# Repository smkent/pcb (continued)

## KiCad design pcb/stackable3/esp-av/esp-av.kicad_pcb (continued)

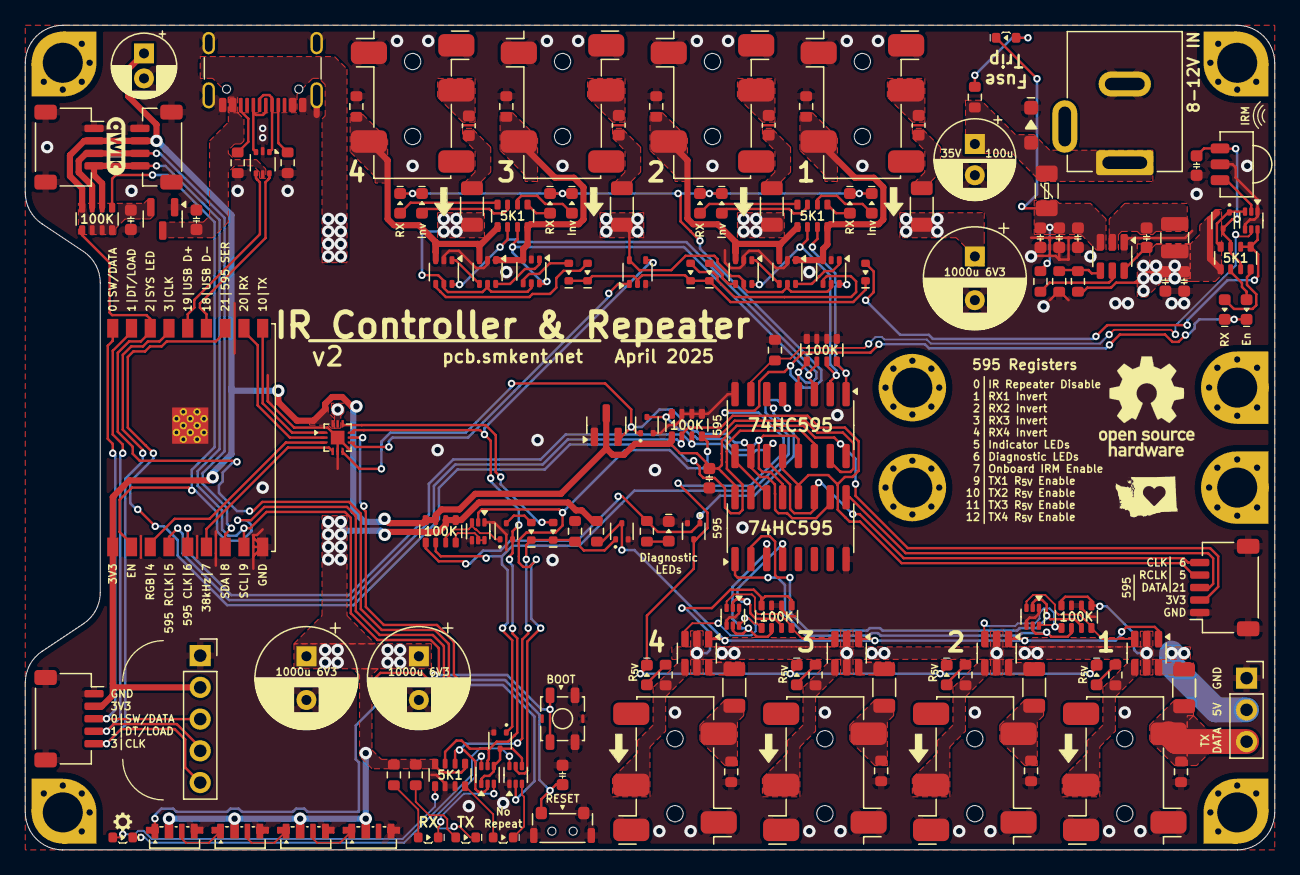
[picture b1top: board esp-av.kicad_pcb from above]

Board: 2 copper layers, 100.0 x 66.0 mm, 146 parts (0 on the bottom side), 124 nets.

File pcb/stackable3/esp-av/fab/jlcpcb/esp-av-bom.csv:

Comment,Designator,Footprint,LCSC
0u1,"C12,C13",discrete:C_0603_1608Metric,
JST SH,J10,connector:JST_SH_SM05B-SRSS-TB_1x05-1MP_P1.00mm_Horizontal,C7433426
USBLC6-2P6,U1,Package_TO_SOT_SMD:SOT-666,C29780639
1u,"C1,C2,C4,C5",discrete:C_0603_1608Metric,
16V 2A,F1,discrete:Fuse_1206_3216Metric,C2982271
ESP32-C3-WROOM-02,SM1,module:ESP32-C3-WROOM-02,
10u,"C3,C10,C11",discrete:C_0603_1608Metric,
Qwiic,J12,connector:Qwiic-SMD-horizontal-logo,C19270571
1000u,"C6,C7,C8",Capacitor_SMD:CP_Elec_8x10,C311227
57K6,R8,Resistor_SMD:R_0603_1608Metric,C23082
74HC595,"U12,U13",Package_SO:SOIC-16_3.9x9.9mm_P1.27mm,
Boot,SW2,Button_Switch_SMD:SW_SPST_TL3342,
Reset,SW1,electromechanical:SW_Push_1P1T-MP_NO_4.6x3mm_Horizontal,C2888932
USB_C_Receptacle_USB2.0_16P,J1,connector:USB_C_Receptacle_GCT_USB4105-xx-A_16P_TopMnt_Horizontal,C2765186
22u,"C14,C15,C19,C20,C21,C22",discrete:C_0603_1608Metric,
5K1,"R1,R2,R16,R18,R19,R20,R22",Resistor_SMD:R_0603_1608Metric,
ME6211C33M5,U2,Package_TO_SOT_SMD:SOT-23-5,C82942
TPS563201,U3,Package_TO_SOT_SMD:SOT-23-6,C116592
10K,"R3,R9",Resistor_SMD:R_0603_1608Metric,
D_TVS,D0,package:D_SOD-123F,C7473216
Pin Socket,J15,Connector_PinSocket_2.54mm:PinSocket_1x03_P2.54mm_Vertical,
Pin socket,J14,Connector_PinSocket_2.54mm:PinSocket_1x05_P2.54mm_Vertical,
4u7,L1,discrete:L_1008_2520Metric,C22471106
XL-1606SURC,LED0,discrete:LED_SideEmitter_1.7x1.1mm,C965860
Qwiic,J13,connector:Qwiic-SMD-vertical,C22390103
DC-005,J0,connector:BarrelJack_DC-005_THT_Horizontal,
Pin socket,J16,Connector_PinSocket_2.54mm:PinSocket_1x07_P2.54mm_Vertical,
1K,R4,Resistor_SMD:R_0603_1608Metric,
100K,"RN3,RN4",discrete:R_Array_Convex_4x0603_HandSolder,C110374
STEMMA-Signal,J11,connector:STEMMA-Signal-SMD-horizontal,C5372880
470u,C16,Capacitor_SMD:CP_Elec_8x10,C7471889
5K1,"RN1,RN5,RN6",discrete:R_Array_Convex_4x0603_HandSolder,C711414
10K,RN2,discrete:R_Array_Convex_4x0603_HandSolder,C110924
PDNM6ET20V05,"Q1,Q7,Q8,Q9",Package_TO_SOT_SMD:SOT-563,C918811
SK6812SIDE-A,"PIX1,PIX2,PIX3,PIX4",discrete:LED_SK6812SIDE-A_4.0x1.6mm,C2890037
SN74LVC1T45Z6,"U10,U11",Package_TO_SOT_SMD:SOT-563,C441819
XL-1606UBC,"LED3,LED4",discrete:LED_SideEmitter_1.7x1.1mm,C965865
XL-1606UWC,"LED1,LED2",discrete:LED_SideEmitter_1.7x1.1mm,C965866
100K,"R5,R6,R7,R17,R21,R23",Resistor_SMD:R_0603_1608Metric,
DMG6968U,Q2,Package_TO_SOT_SMD:SOT-23,C150759
Warm White,LED13,discrete:LED_0603_1608Metric,C2827262
Pink,"LED9,LED10,LED11,LED12,LED14,LED15,LED16,LED17",discrete:LED_0603_1608Metric,C7496826
SN74LVC1G157DC,"U6,U7,U8,U9",package:SOT-363_SC-70-6_HandSolder,C22469913
1N4148WS,"D1,D2,D3,D4,D5,D6",package:D_SOD-323,
PJ-327U,"J2,J3,J4,J5,J6,J7,J8,J9",connector:Jack_3.5mm_PJ-327U-SMT_Horizontal,C397453
Ice Blue,"LED5,LED6,LED7,LED8",discrete:LED_0603_1608Metric,
NC7WZ14P6X,"U4,U5",package:SOT-363_SC-70-6_HandSolder,C5207816
15R4,"R12,R13,R14,R15",Resistor_SMD:R_1206_3216Metric,C3013373
DMP1045U,"Q3,Q4,Q5,Q6,Q10,Q11,Q12,Q13,Q14",Package_TO_SOT_SMD:SOT-23,C177033
2K2,"R10,R11",Resistor_SMD:R_0603_1608Metric,

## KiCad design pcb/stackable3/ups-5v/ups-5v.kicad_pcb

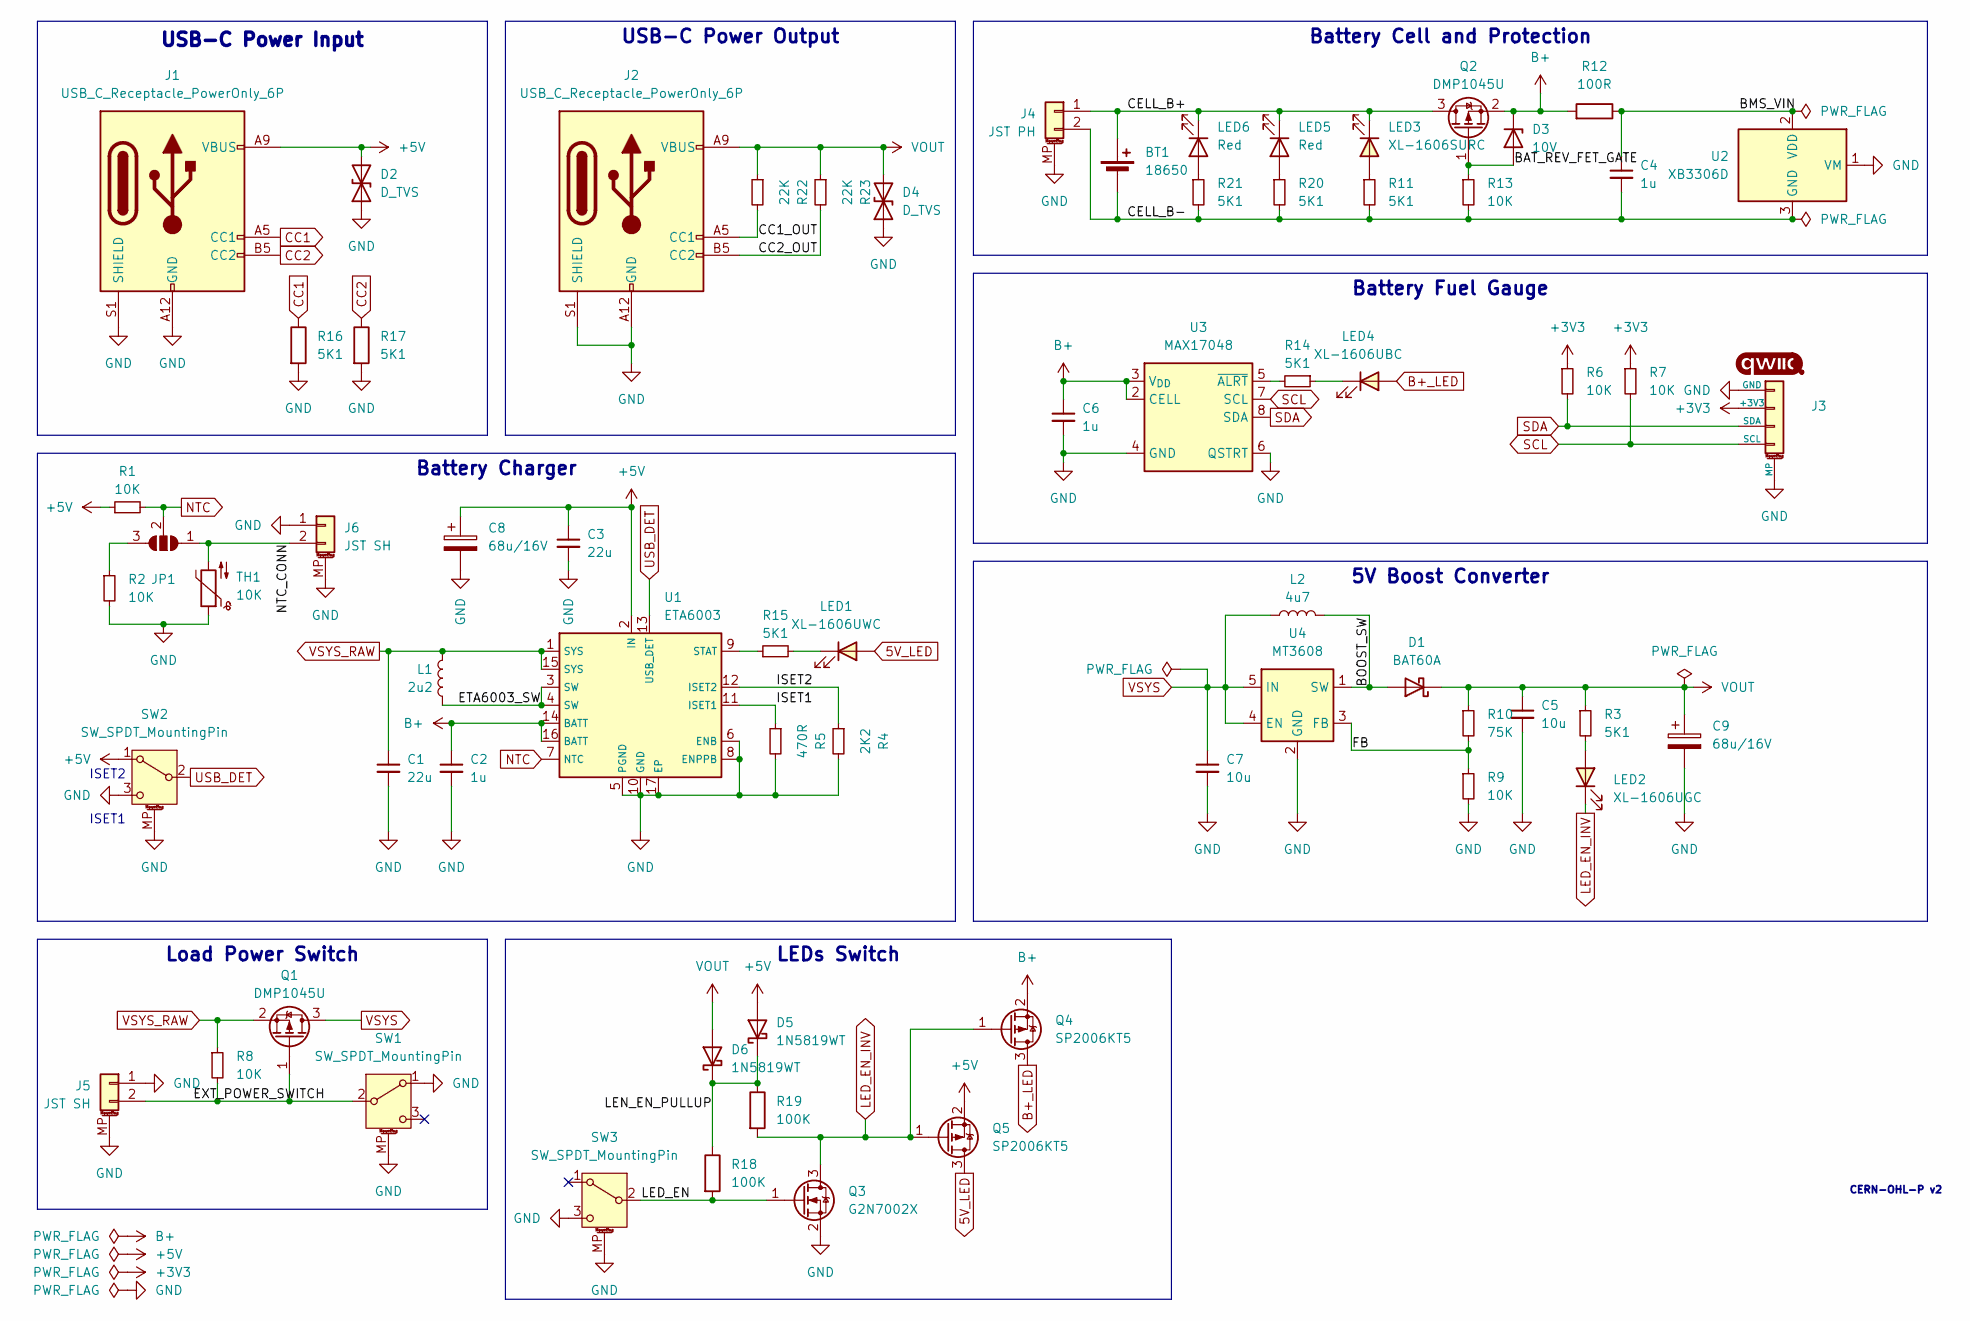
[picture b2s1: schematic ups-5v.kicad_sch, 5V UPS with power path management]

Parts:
BT1: 18650; BatteryHolder_1x18650_THT
C1: 22u; C_0603_1608Metric; LCSC Part C86295
C2, C4, C6: 1u; C_0603_1608Metric; LCSC Part C5199872
C3: 22u; C_0805_2012Metric; LCSC Part C602037
C5, C7: 10u; C_0603_1608Metric; LCSC Part C22367825
C8, C9: 68u/16V; CP_Radial_D6.3mm_P2.50mm; LCSC Part C2976197
D1: BAT60A; D_SOD-323; LCSC Part C7502695
D2, D4: D_TVS; D_SOD-882; LCSC Part C45961
D3: 10V; D_SOD-523; LCSC Part C2832579
D5, D6: 1N5819WT; D_SOD-523; LCSC Part C20754784
J1, J2: USB_C_Receptacle_PowerOnly_6P; USB_C_Receptacle_GCT_USB4125-xx-x_6P_TopMnt_Horizontal_Hand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; LCSC Part C2927029
J3: Qwiic; Qwiic-SMD-horizontal-logo; LCSC Part C19270571
J4: JST PH; JST_PH_S2B-PH-SM4-TB_1x02-1MP_P2.00mm_Horizontal; LCSC Part C18221575
J5, J6: JST SH; JST_SH_SM02B-SRSS-TB_1x02-1MP_P1.00mm_Horizontal; LCSC Part C7433423
JP1: SolderJumper_3_Open; SolderJumper-3_P1.3mm_Open_RoundedPad1.0x1.5mm
L1: 2u2; L_1008_2520Metric; LCSC Part C5832372
L2: 4u7; L_1008_2520Metric; LCSC Part C22471106
LED1: XL-1606UWC; LED_SideEmitter_1.7x1.1mm; LCSC Part C965866
LED2: XL-1606UGC; LED_SideEmitter_1.7x1.1mm; LCSC Part C965863
LED3: XL-1606SURC; LED_SideEmitter_1.7x1.1mm; LCSC Part C965860
LED4: XL-1606UBC; LED_SideEmitter_1.7x1.1mm; LCSC Part C965865
LED5, LED6: Red; LED_0603_1608Metric; LCSC Part C7371906
Q1, Q2: DMP1045U; SOT-23; LCSC Part C177033
Q3: G2N7002X; SOT-523; LCSC Part C5258971
Q4, Q5: SP2006KT5; SOT-523; LCSC Part C41355141
R1, R2, R6, R7, R8, R9, R13: 10K; R_0603_1608Metric; LCSC Part C25804
R3: 5K1; R_0603_1608Metric; LCSC Part C23186
R4: 2K2; R_0603_1608Metric; LCSC Part C4190
R5: 470R; R_0603_1608Metric; LCSC Part C23179
R10: 75K; R_0603_1608Metric; LCSC Part C23242
R11, R14, R15, R16, R17, R20, R21: 5K1; R_0603_1608Metric; LCSC Part C25905
R12: 100R; R_0603_1608Metric; LCSC Part C25076
R18, R19: 100K; R_0603_1608Metric; LCSC Part C25803
R22, R23: 22K; R_0603_1608Metric; LCSC Part C31850
SW1, SW2, SW3: SW_SPDT_MountingPin; SW_SPDT_PCM12; LCSC Part C319020
TH1: 10K; JST_SH_SM02B-SRSS-TB_1x02-1MP_P1.00mm_Horizontal
U1: ETA6003; QFN-16-1EP_3x3mm_P0.5mm_EP1.7x1.7mm_ThermalVias_ETA6003; LCSC Part C5455585
U2: XB3306D; SOT-23; LCSC Part C2759992
U3: MAX17048; TDFN-8-1EP_2x2mm_P0.5mm_EP0.8x1.2mm; LCSC Part C2682616
U4: MT3608; SOT-23-6; LCSC Part C84817

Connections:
5V_LED: LED1.2 (A), Q5.3 (D)
+3V3: J3.2 (+3V3), R6.1, R7.1
+5V: C3.1, C8.1, D2.2 (A2), D5.2 (A), J1.A9 (VBUS), J1.B9 (VBUS), Q5.2 (S), R1.1, SW2.1 (A), U1.2 (IN)
/BAT_REV_FET_GATE: D3.2 (A), Q2.1 (G), R13.1
/BMS_VIN: C4.1, R12.1, U2.2 (VDD)
/BOOST_SW: D1.2 (A), L2.2, U4.1 (SW)
/CC1_OUT: J2.A5 (CC1), R22.2
/CC2_OUT: J2.B5 (CC2), R23.2
/CELL_B+: BT1.1 (+), J4.1, LED3.1 (K), LED5.1 (K), LED6.1 (K), Q2.3 (D)
/CELL_B-: BT1.2 (-), C4.2, J4.2, R11.2, R13.2, R20.2, R21.2, U2.3 (GND)
/ETA6003_SW: L1.2, U1.3 (SW), U1.4 (SW)
/EXT_POWER_SWITCH: J5.2, Q1.1 (G), R8.2, SW1.2 (B)
/FB: R9.1, R10.2, U4.3 (FB)
/ISET1: R5.1, U1.11 (ISET1)
/ISET2: R4.1, U1.12 (ISET2)
/LED_EN: Q3.1 (G), R18.2, SW3.2 (B)
/LEN_EN_PULLUP: D5.1 (K), D6.1 (K), R18.1, R19.1
/NTC_CONN: J6.2, JP1.1 (A), TH1.2
B+: C2.1, C6.1, D3.1 (K), Q2.2 (S), Q4.2 (S), R12.2, U1.14 (BATT), U1.16 (BATT), U3.2 (CELL), U3.3 (V_{DD})
B+_LED: LED4.2 (A), Q4.3 (D)
CC1: J1.A5 (CC1), R16.1
CC2: J1.B5 (CC2), R17.1
GND: C1.2, C2.2, C3.2, C5.2, C6.2, C7.2, C8.2, C9.2, D2.1 (A1), D4.1 (A1), J1.A12 (GND), J1.B12 (GND), J1.S1 (SHIELD), J2.A12 (GND), J2.B12 (GND), J2.S1 (SHIELD), J3.1 (GND), J3.MP, J4.MP (MountPin), J5.1, J5.MP (MountPin), J6.1, J6.MP (MountPin), Q3.2 (S), R2.2, R4.2, R5.2, R9.2, R16.2, R17.2, SW1.1 (A), SW1.MP (MountPin), SW2.3 (C), SW2.MP (MountPin), SW3.3 (C), SW3.MP (MountPin), TH1.1, U1.5 (PGND), U1.6 (ENB), U1.8 (ENPPB), U1.10 (GND), U1.17 (EP), U2.1 (VM), U3.1 (CTG), U3.4 (GND), U3.6 (QSTRT), U3.9 (EP), U4.2 (GND)
LED_EN_INV: LED2.1 (K), Q3.3 (D), Q4.1 (G), Q5.1 (G), R19.2
NTC: JP1.2 (C), R1.2, U1.7 (NTC)
unnamed: JP1.3 (B), R2.1
unnamed: LED1.1 (K), R15.2
unnamed: LED2.2 (A), R3.2
unnamed: LED3.2 (A), R11.1
unnamed: LED4.1 (K), R14.1
unnamed: LED5.2 (A), R20.1
unnamed: LED6.2 (A), R21.1
unnamed: R15.1, U1.9 (STAT)
unnamed: R14.2, U3.5 (~ALRT)
SCL: J3.4 (SCL), R7.2, U3.7 (SCL)
SDA: J3.3 (SDA), R6.2, U3.8 (SDA)
USB_DET: SW2.2 (B), U1.13 (USB_DET)
VOUT: C5.1, C9.1, D1.1 (K), D4.2 (A2), D6.2 (A), J2.A9 (VBUS), J2.B9 (VBUS), R3.1, R10.1, R22.1, R23.1
VSYS: C7.1, L2.1, Q1.3 (D), U4.4 (EN), U4.5 (IN)
VSYS_RAW: C1.1, L1.1, Q1.2 (S), R8.1, U1.1 (SYS), U1.15 (SYS)

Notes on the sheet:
CERN-OHL-P v2
ISET1
ISET2
5V Boost Converter
USB-C Power Output
Battery Fuel Gauge
USB-C Power Input
Battery Cell and Protection
LEDs Switch
Load Power Switch
Battery Charger

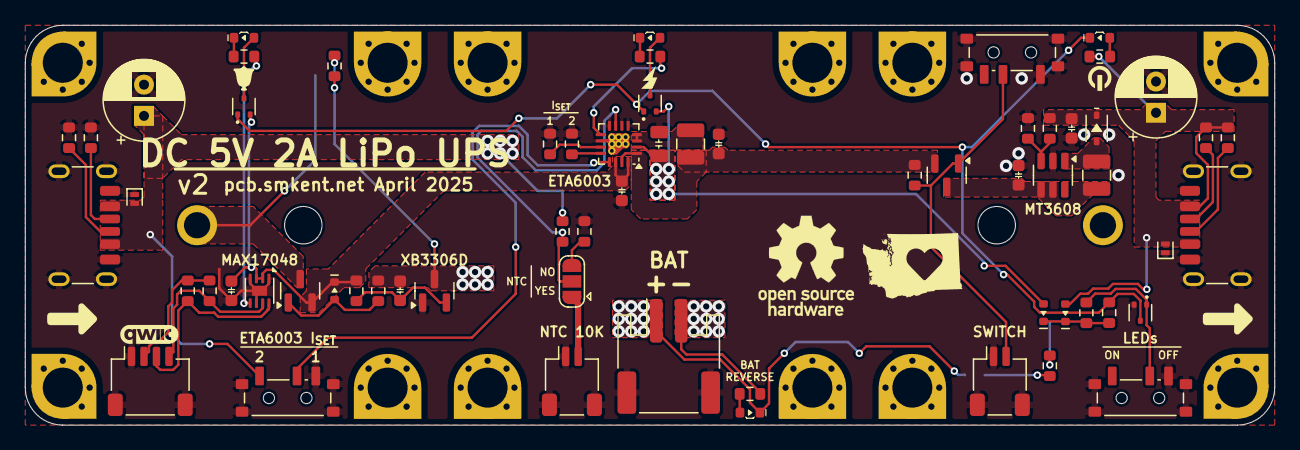
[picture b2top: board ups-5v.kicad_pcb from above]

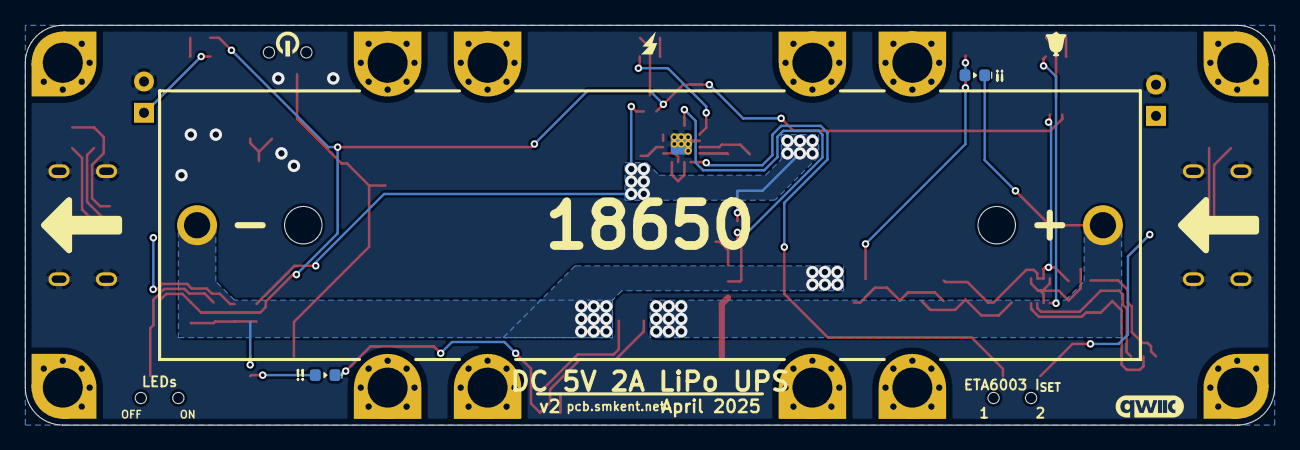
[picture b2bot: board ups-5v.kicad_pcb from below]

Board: 2 copper layers, 100.0 x 32.0 mm, 66 parts (3 on the bottom side), 40 nets.

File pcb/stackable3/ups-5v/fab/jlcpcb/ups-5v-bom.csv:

Comment,Designator,Footprint,LCSC
SW_SPDT_MountingPin,"SW1,SW2,SW3",electromechanical:SW_SPDT_PCM12,C319020
10K,"R1,R2,R6,R7,R8,R9,R13",Resistor_SMD:R_0603_1608Metric,C25804
2u2,L1,discrete:L_1008_2520Metric,C5832372
SP2006KT5,"Q4,Q5",package:SOT-523,C41355141
5K1,"R11,R14,R15,R16,R17,R20,R21",Resistor_SMD:R_0603_1608Metric,C25905
22u,C1,discrete:C_0603_1608Metric,C86295
10u,"C5,C7",discrete:C_0603_1608Metric,C22367825
22u,C3,discrete:C_0805_2012Metric,C602037
100K,"R18,R19",Resistor_SMD:R_0603_1608Metric,C25803
22K,"R22,R23",Resistor_SMD:R_0603_1608Metric,C31850
JST SH,"J5,J6",connector:JST_SH_SM02B-SRSS-TB_1x02-1MP_P1.00mm_Horizontal,C7433423
D_TVS,"D2,D4",Diode_SMD:D_SOD-882,C45961
68u/16V,"C8,C9",Capacitor_THT:CP_Radial_D6.3mm_P2.50mm,C2976197
Red,"LED5,LED6",discrete:LED_0603_1608Metric,C7371906
100R,R12,Resistor_SMD:R_0603_1608Metric,C25076
USB_C_Receptacle_PowerOnly_6P,"J1,J2",connector:USB_C_Receptacle_GCT_USB4125-xx-x_6P_TopMnt_Horizontal_HandSolder,C2927029
MAX17048,U3,package:TDFN-8-1EP_2x2mm_P0.5mm_EP0.8x1.2mm,C2682616
Qwiic,J3,connector:Qwiic-SMD-horizontal-logo,C19270571
G2N7002X,Q3,package:SOT-523,C5258971
XL-1606UBC,LED4,discrete:LED_SideEmitter_1.7x1.1mm,C965865
1u,"C2,C4,C6",discrete:C_0603_1608Metric,C5199872
75K,R10,Resistor_SMD:R_0603_1608Metric,C23242
18650,BT1,connector:BatteryHolder_1x18650_THT,
10V,D3,package:D_SOD-523,C2832579
1N5819WT,"D5,D6",package:D_SOD-523,C20754784
XB3306D,U2,Package_TO_SOT_SMD:SOT-23,C2759992
470R,R5,Resistor_SMD:R_0603_1608Metric,C23179
XL-1606SURC,LED3,discrete:LED_SideEmitter_1.7x1.1mm,C965860
4u7,L2,discrete:L_1008_2520Metric,C22471106
BAT60A,D1,package:D_SOD-323,C7502695
XL-1606UWC,LED1,discrete:LED_SideEmitter_1.7x1.1mm,C965866
ETA6003,U1,package:QFN-16-1EP_3x3mm_P0.5mm_EP1.7x1.7mm_ThermalVias_ETA6003,C5455585
2K2,R4,Resistor_SMD:R_0603_1608Metric,C4190
DMP1045U,"Q1,Q2",Package_TO_SOT_SMD:SOT-23,C177033
MT3608,U4,Package_TO_SOT_SMD:SOT-23-6,C84817
5K1,R3,Resistor_SMD:R_0603_1608Metric,C23186
JST PH,J4,connector:JST_PH_S2B-PH-SM4-TB_1x02-1MP_P2.00mm_Horizontal,C18221575
XL-1606UGC,LED2,discrete:LED_SideEmitter_1.7x1.1mm,C965863

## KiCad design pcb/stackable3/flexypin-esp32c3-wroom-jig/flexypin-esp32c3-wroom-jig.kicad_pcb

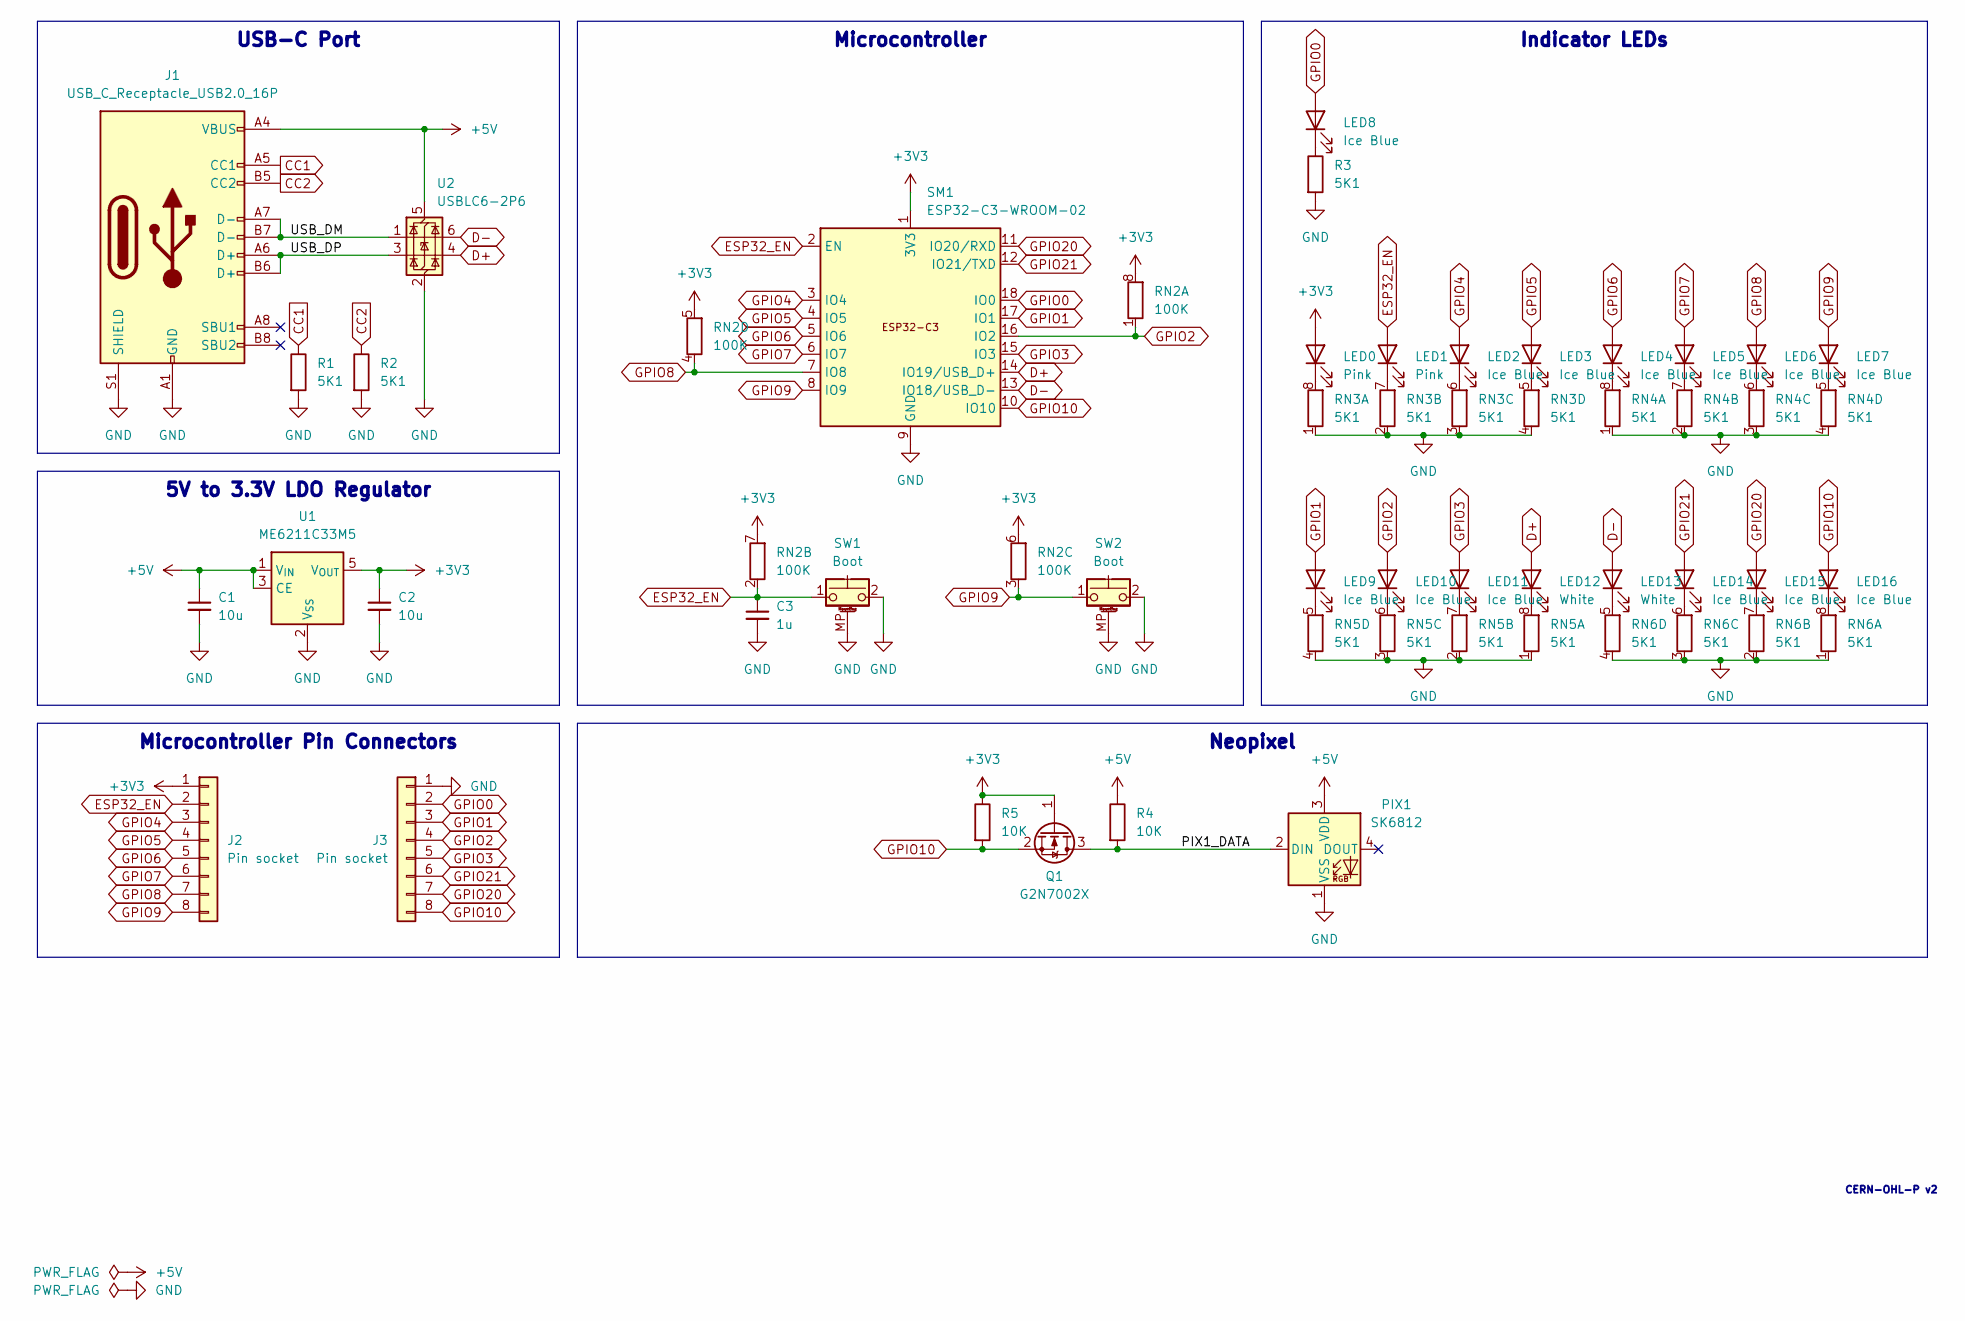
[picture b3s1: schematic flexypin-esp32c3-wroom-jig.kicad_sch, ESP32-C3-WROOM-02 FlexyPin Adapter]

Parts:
C1, C2: 10u; C_0402_1005Metric; LCSC Part C315248
C3: 1u; C_0402_1005Metric; LCSC Part C52923
J1: USB_C_Receptacle_USB2.0_16P; USB_C_Receptacle_GCT_USB4105-xx-A_16P_TopMnt_Horizontal; LCSC Part C2765186
J2, J3: Pin socket; PinSocket_1x08_P2.54mm_Vertical
LED0, LED1: Pink; LED_0402_1005Metric; LCSC Part C779449
LED2, LED3, LED4, LED5, LED6, LED7, LED8, LED9, LED10, LED11, LED14, LED15, LED16: Ice Blue; LED_0402_1005Metric; LCSC Part C7496805
LED12, LED13: White; LED_0402_1005Metric; LCSC Part C20613596
PIX1: SK6812; LED_SK6812_PLCC4_5.0x5.0mm_P3.2mm
Q1: G2N7002X; SOT-523; LCSC Part C5258971
R1, R2: 5K1; R_0603_1608Metric; LCSC Part C23186
R3: 5K1; R_0402_1005Metric; LCSC Part C25905
R4, R5: 10K; R_0603_1608Metric; LCSC Part C25804
RN2: 100K; R_Array_Convex_4x0402_HandSolder; LCSC Part C110374
RN3, RN4, RN5, RN6: 5K1; R_Array_Convex_4x0402_HandSolder; LCSC Part C425290
SM1: ESP32-C3-WROOM-02; ESP32-C3-WROOM-02-FlexyPin
SW1, SW2: Boot; SW_Push_1P1T_NO_3.3x3.3mm_MP
U1: ME6211C33M5; SOT-23-5; LCSC Part C82942
U2: USBLC6-2P6; SOT-666; LCSC Part C29780639

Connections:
+3V3: C2.1, J2.1, LED0.2 (A), Q1.1 (G), R5.1, RN2.5 (R4.2), RN2.6 (R3.2), RN2.7 (R2.2), RN2.8 (R1.2), SM1.1 (3V3), U1.5 (V_{OUT})
+5V: C1.1, J1.A4 (VBUS), J1.A9 (VBUS), J1.B4 (VBUS), J1.B9 (VBUS), PIX1.3 (VDD), R4.1, U1.1 (V_{IN}), U1.3 (CE), U2.5 (VBUS)
/PIX1_DATA: PIX1.2 (DIN), Q1.3 (D), R4.2
/USB_DM: J1.A7 (D-), J1.B7 (D-), U2.1 (I/O1)
/USB_DP: J1.A6 (D+), J1.B6 (D+), U2.3 (I/O2)
CC1: J1.A5 (CC1), R1.1
CC2: J1.B5 (CC2), R2.1
D+: LED12.2 (A), SM1.14 (IO19/USB_D+), U2.4 (I/O2)
D-: LED13.2 (A), SM1.13 (IO18/USB_D-), U2.6 (I/O1)
ESP32_EN: C3.1, J2.2, LED1.2 (A), RN2.2 (R2.1), SM1.2 (EN), SW1.1
GND: C1.2, C2.2, C3.2, J1.A1 (GND), J1.A12 (GND), J1.B1 (GND), J1.B12 (GND), J1.S1 (SHIELD), J3.1, PIX1.1 (VSS), R1.2, R2.2, R3.2, RN3.1 (R1.1), RN3.2 (R2.1), RN3.3 (R3.1), RN3.4 (R4.1), RN4.1 (R1.1), RN4.2 (R2.1), RN4.3 (R3.1), RN4.4 (R4.1), RN5.1 (R1.1), RN5.2 (R2.1), RN5.3 (R3.1), RN5.4 (R4.1), RN6.1 (R1.1), RN6.2 (R2.1), RN6.3 (R3.1), RN6.4 (R4.1), SM1.9 (GND), SM1.19 (GND), SW1.2, SW1.MP (MountPin), SW2.2, SW2.MP (MountPin), U1.2 (V_{SS}), U2.2 (GND)
GPIO0: J3.2, LED8.2 (A), SM1.18 (IO0)
GPIO1: J3.3, LED9.2 (A), SM1.17 (IO1)
GPIO2: J3.4, LED10.2 (A), RN2.1 (R1.1), SM1.16 (IO2)
GPIO3: J3.5, LED11.2 (A), SM1.15 (IO3)
GPIO4: J2.3, LED2.2 (A), SM1.3 (IO4)
GPIO5: J2.4, LED3.2 (A), SM1.4 (IO5)
GPIO6: J2.5, LED4.2 (A), SM1.5 (IO6)
GPIO7: J2.6, LED5.2 (A), SM1.6 (IO7)
GPIO8: J2.7, LED6.2 (A), RN2.4 (R4.1), SM1.7 (IO8)
GPIO9: J2.8, LED7.2 (A), RN2.3 (R3.1), SM1.8 (IO9), SW2.1
GPIO10: J3.8, LED16.2 (A), Q1.2 (S), R5.2, SM1.10 (IO10)
GPIO20: J3.7, LED15.2 (A), SM1.11 (IO20/RXD)
GPIO21: J3.6, LED14.2 (A), SM1.12 (IO21/TXD)
unnamed: LED0.1 (K), RN3.8 (R1.2)
unnamed: LED1.1 (K), RN3.7 (R2.2)
unnamed: LED2.1 (K), RN3.6 (R3.2)
unnamed: LED3.1 (K), RN3.5 (R4.2)
unnamed: LED4.1 (K), RN4.8 (R1.2)
unnamed: LED5.1 (K), RN4.7 (R2.2)
unnamed: LED6.1 (K), RN4.6 (R3.2)
unnamed: LED7.1 (K), RN4.5 (R4.2)
unnamed: LED8.1 (K), R3.1
unnamed: LED9.1 (K), RN5.5 (R4.2)
unnamed: LED10.1 (K), RN5.6 (R3.2)
unnamed: LED11.1 (K), RN5.7 (R2.2)
unnamed: LED12.1 (K), RN5.8 (R1.2)
unnamed: LED13.1 (K), RN6.5 (R4.2)
unnamed: LED14.1 (K), RN6.6 (R3.2)
unnamed: LED15.1 (K), RN6.7 (R2.2)
unnamed: LED16.1 (K), RN6.8 (R1.2)

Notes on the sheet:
CERN-OHL-P v2
Indicator LEDs
Neopixel
Microcontroller Pin Connectors
5V to 3.3V LDO Regulator
USB-C Port
Microcontroller

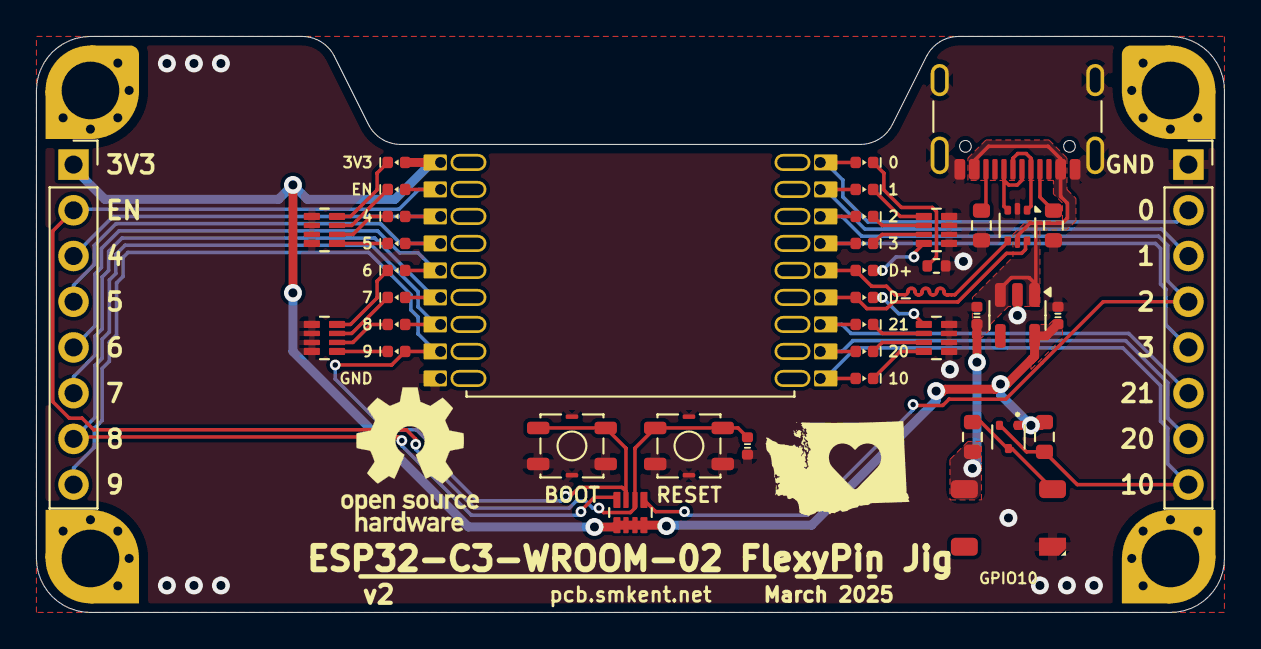
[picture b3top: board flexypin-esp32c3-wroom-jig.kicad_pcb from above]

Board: 2 copper layers, 66.0 x 32.0 mm, 40 parts (0 on the bottom side), 41 nets.

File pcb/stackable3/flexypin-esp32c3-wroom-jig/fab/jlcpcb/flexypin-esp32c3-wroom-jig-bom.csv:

Comment,Designator,Footprint,LCSC
5K1,"RN3,RN4,RN5,RN6",discrete:R_Array_Convex_4x0402_HandSolder,C425290
Ice Blue,"LED2,LED3,LED4,LED5,LED6,LED7,LED8,LED9,LED10,LED11,LED14,LED15,LED16",discrete:LED_0402_1005Metric,C7496805
10u,"C1,C2",discrete:C_0402_1005Metric,C315248
G2N7002X,Q1,package:SOT-523,C5258971
Pin socket,"J2,J3",Connector_PinSocket_2.54mm:PinSocket_1x08_P2.54mm_Vertical,
White,"LED12,LED13",discrete:LED_0402_1005Metric,C20613596
ME6211C33M5,U1,Package_TO_SOT_SMD:SOT-23-5,C82942
Boot,"SW1,SW2",electromechanical:SW_Push_1P1T_NO_3.3x3.3mm_MP,
5K1,"R1,R2",Resistor_SMD:R_0603_1608Metric,C23186
USB_C_Receptacle_USB2.0_16P,J1,connector:USB_C_Receptacle_GCT_USB4105-xx-A_16P_TopMnt_Horizontal,C2765186
Pink,"LED0,LED1",discrete:LED_0402_1005Metric,C779449
5K1,R3,Resistor_SMD:R_0402_1005Metric,C25905
SK6812,PIX1,discrete:LED_SK6812_PLCC4_5.0x5.0mm_P3.2mm,
ESP32-C3-WROOM-02,SM1,module:ESP32-C3-WROOM-02-FlexyPin,
10K,"R4,R5",Resistor_SMD:R_0603_1608Metric,C25804
USBLC6-2P6,U2,Package_TO_SOT_SMD:SOT-666,C29780639
100K,RN2,discrete:R_Array_Convex_4x0402_HandSolder,C110374
1u,C3,discrete:C_0402_1005Metric,C52923

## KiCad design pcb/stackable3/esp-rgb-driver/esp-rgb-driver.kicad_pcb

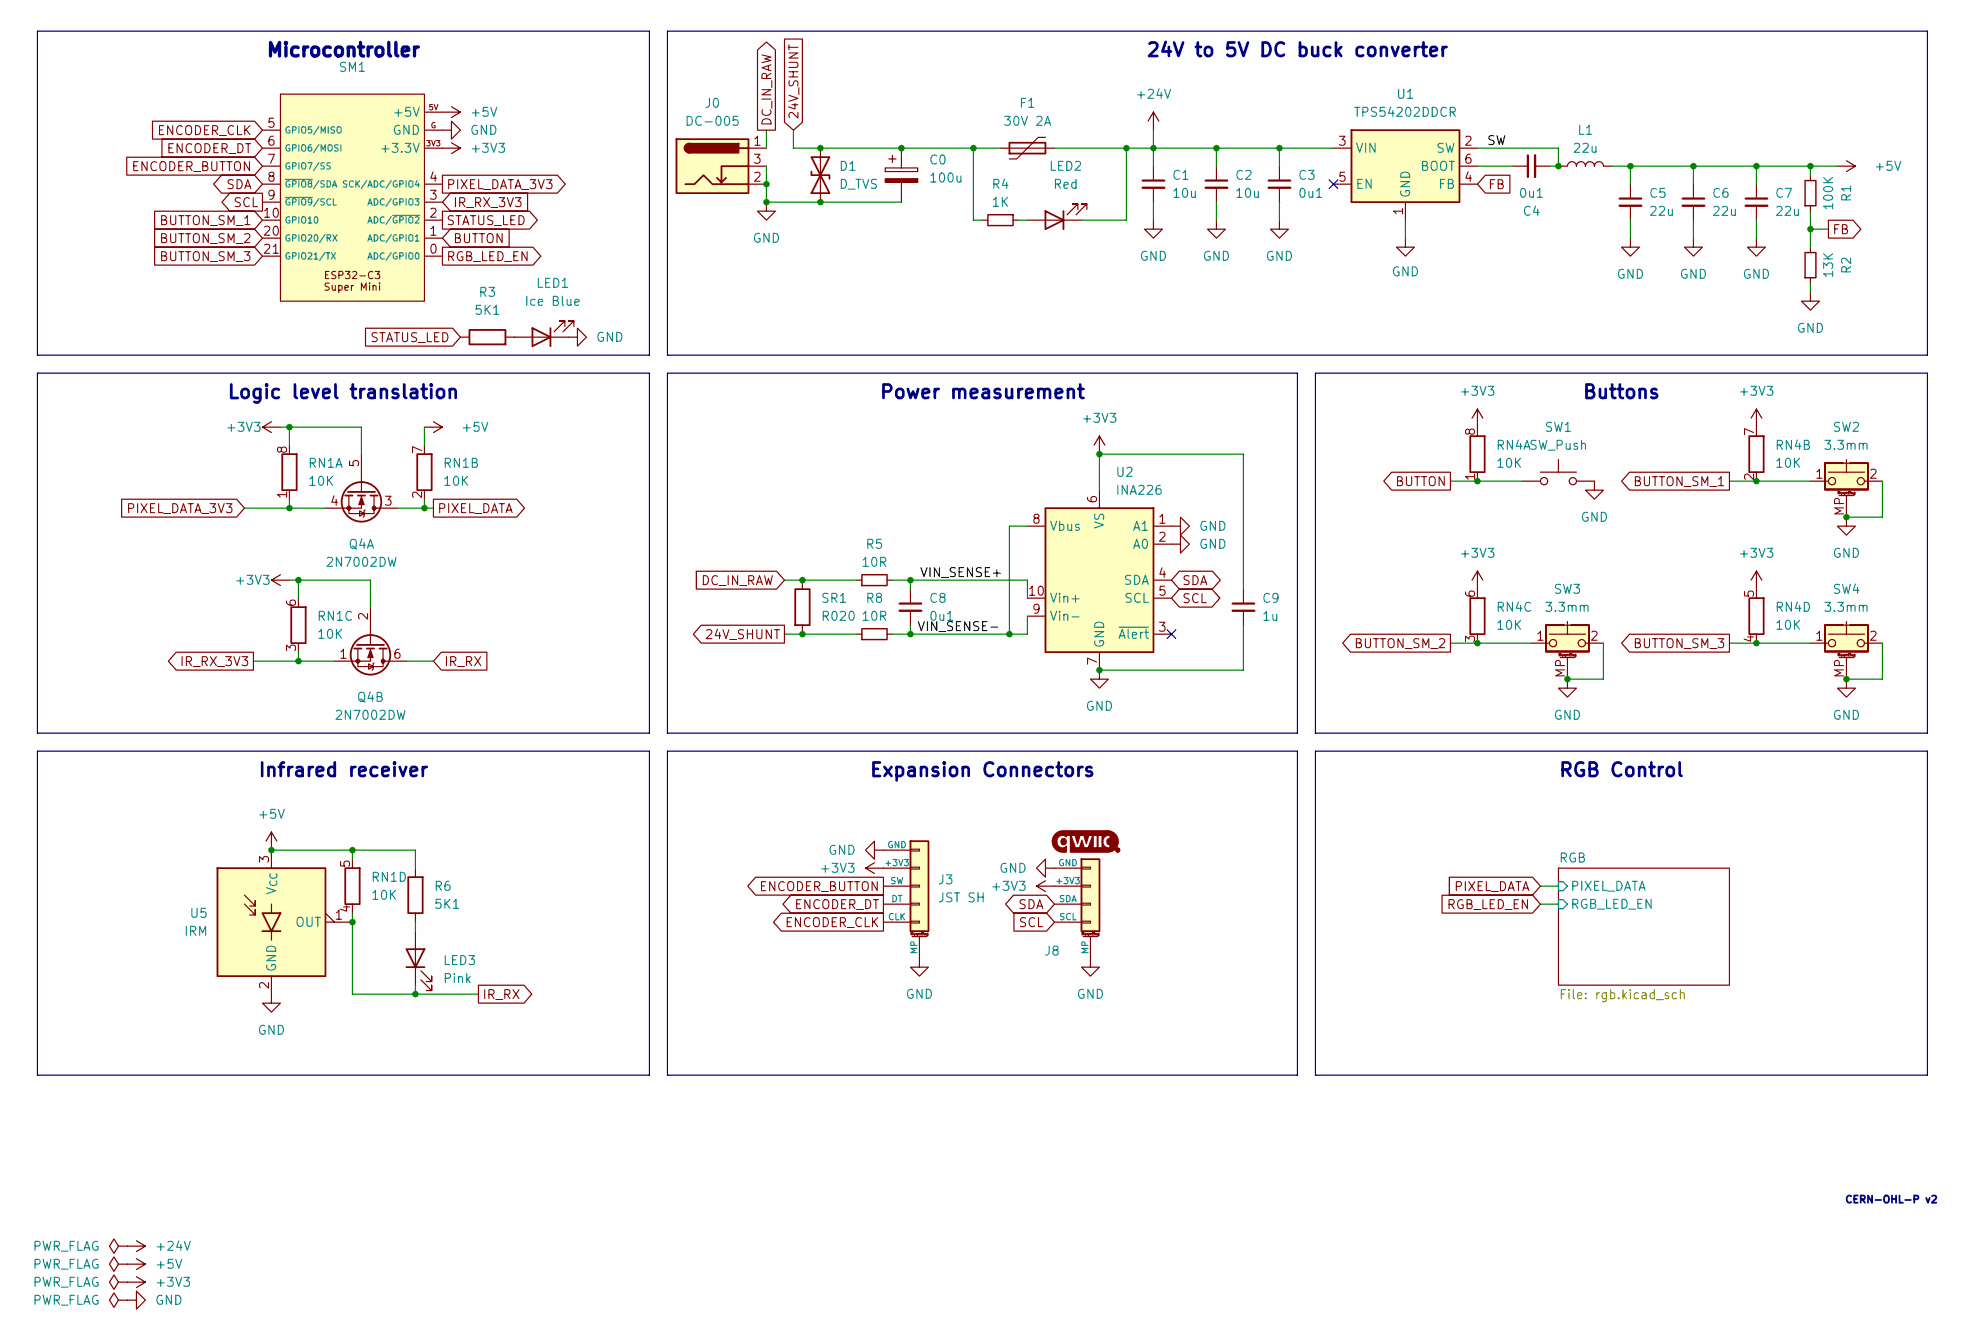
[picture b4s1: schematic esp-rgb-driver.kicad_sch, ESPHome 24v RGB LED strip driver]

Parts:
C0: 100u; CP_Radial_D6.3mm_P2.50mm; LCSC Part C7471889
C1, C2: 10u; C_0603_1608Metric
C3, C4: 0u1; C_0402_1005Metric
C5, C6, C7: 22u; C_0603_1608Metric
C8: 0u1; C_0402_1005Metric; LCSC Part C152814
C9: 1u; C_0402_1005Metric
D1: D_TVS; D_SOD-123F; LCSC Part C7473232
F1: 30V 2A; Fuse_1812_4532Metric; LCSC Part C22366122
J0: DC-005; BarrelJack_DC-005_THT_Horizontal
J3: JST SH; JST_SH_SM05B-SRSS-TB_1x05-1MP_P1.00mm_Horizontal; LCSC Part C7433426
J8: Qwiic; Qwiic-SMD-horizontal-logo; LCSC Part C19270571
L1: 22u; L_1008_2520Metric
LED1: Ice Blue; LED_0603_1608Metric
LED2: Red; LED_0402_1005Metric
LED3: Pink; LED_0402_1005Metric
Q4: 2N7002DW; SOT-363_SC-70-6; LCSC Part C5190214
R1: 100K; R_0603_1608Metric
R2: 13K; R_0603_1608Metric; LCSC Part C22797
R3, R6: 5K1; R_0402_1005Metric
R4: 1K; R_0402_1005Metric
R5, R8: 10R; R_0402_1005Metric; LCSC Part C25077
RN1: 10K; R_Array_Convex_4x0603
RN4: 10K; R_Array_Convex_4x0603; LCSC Part C110924
SM1: ESP32-C3-Super-Mini-Castellated-SMD-only
SR1: R020; R_2512_6332Metric_Pad1.40x3.35mm_HandSolder; LCSC Part C5375467
SW1: SW_Push; SW_SPST_PTS647_Sx50; LCSC Part C22459537
SW2, SW3, SW4: 3.3mm; SW_Push_1P1T_NO_3.3x3.3mm_MP
U1: TPS54202DDCR; SOT-23-6; LCSC Part C191884
U2: INA226; VSSOP-10_3x3mm_P0.5mm; LCSC Part C49851
U5: IRM; IRM_5.0x5.0mm_SIP-3_P1.27mm_THT; LCSC Part C7433078

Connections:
24V_SHUNT: C0.1, D1.2 (A2), F1.1, R4.2, R8.1, SR1.2
+3V3: C9.1, J3.2 (+3V3), J8.2 (+3V3), Q4.2 (G), Q4.5 (G), RN1.6 (R3.2), RN1.8 (R1.2), RN4.5 (R4.2), RN4.6 (R3.2), RN4.7 (R2.2), RN4.8 (R1.2), SM1.3V3 (+3.3V), U2.6 (VS)
+5V: C5.1, C6.1, C7.1, L1.2, R1.2, R6.2, RN1.5 (R4.2), RN1.7 (R2.2), SM1.5V (+5V), U5.3 (V_{CC}); also elsewhere on the board
+24V: C1.1, C2.1, C3.1, F1.2, LED2.1 (K), U1.3 (VIN); also elsewhere on the board
/SW: C4.2, L1.1, U1.2 (SW)
/VIN_SENSE+: C8.1, R5.2, U2.10 (Vin+)
/VIN_SENSE-: C8.2, R8.2, U2.8 (Vbus), U2.9 (Vin-)
BUTTON: RN4.1 (R1.1), SM1.1 (ADC/GPIO1), SW1.1
BUTTON_SM_1: RN4.2 (R2.1), SM1.10 (GPIO10), SW2.1
BUTTON_SM_2: RN4.3 (R3.1), SM1.20 (GPIO20/RX), SW3.1
BUTTON_SM_3: RN4.4 (R4.1), SM1.21 (GPIO21/TX), SW4.1
DC_IN_RAW: J0.1, R5.1, SR1.1
ENCODER_BUTTON: J3.3 (SW), SM1.7 (GPIO7/SS)
ENCODER_CLK: J3.5 (CLK), SM1.5 (GPIO5/MISO)
ENCODER_DT: J3.4 (DT), SM1.6 (GPIO6/MOSI)
FB: R1.1, R2.2, U1.4 (FB)
GND: C0.2, C1.2, C2.2, C3.2, C5.2, C6.2, C7.2, C9.2, D1.1 (A1), J0.2, J0.3, J3.1 (GND), J3.MP, J8.1 (GND), J8.MP, LED1.1 (K), R2.1, SM1.G (GND), SW1.2, SW2.2, SW2.MP (MountPin), SW3.2, SW3.MP (MountPin), SW4.2, SW4.MP (MountPin), U1.1 (GND), U2.1 (A1), U2.2 (A0), U2.7 (GND), U5.2 (GND); also elsewhere on the board
IR_RX: LED3.1 (K), Q4.6 (D), RN1.4 (R4.1), U5.1 (OUT)
IR_RX_3V3: Q4.1 (S), RN1.3 (R3.1), SM1.3 (ADC/GPIO3)
unnamed: LED1.2 (A), R3.2
unnamed: LED2.2 (A), R4.1
unnamed: LED3.2 (A), R6.1
unnamed: C4.1, U1.6 (BOOT)
PIXEL_DATA: Q4.3 (D), RN1.2 (R2.1); also elsewhere on the board
PIXEL_DATA_3V3: Q4.4 (S), RN1.1 (R1.1), SM1.4 (SCK/ADC/GPIO4)
RGB_LED_EN: SM1.0 (ADC/GPIO0); also elsewhere on the board
SCL: J8.4 (SCL), SM1.9 (~GPIO9/SCL), U2.5 (SCL)
SDA: J8.3 (SDA), SM1.8 (~GPIO8/SDA), U2.4 (SDA)
STATUS_LED: R3.1, SM1.2 (ADC/~GPIO2)

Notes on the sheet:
Power measurement
Logic level translation
24V to 5V DC buck converter
Infrared receiver
Expansion Connectors
RGB Control
Microcontroller
Buttons
CERN-OHL-P v2
